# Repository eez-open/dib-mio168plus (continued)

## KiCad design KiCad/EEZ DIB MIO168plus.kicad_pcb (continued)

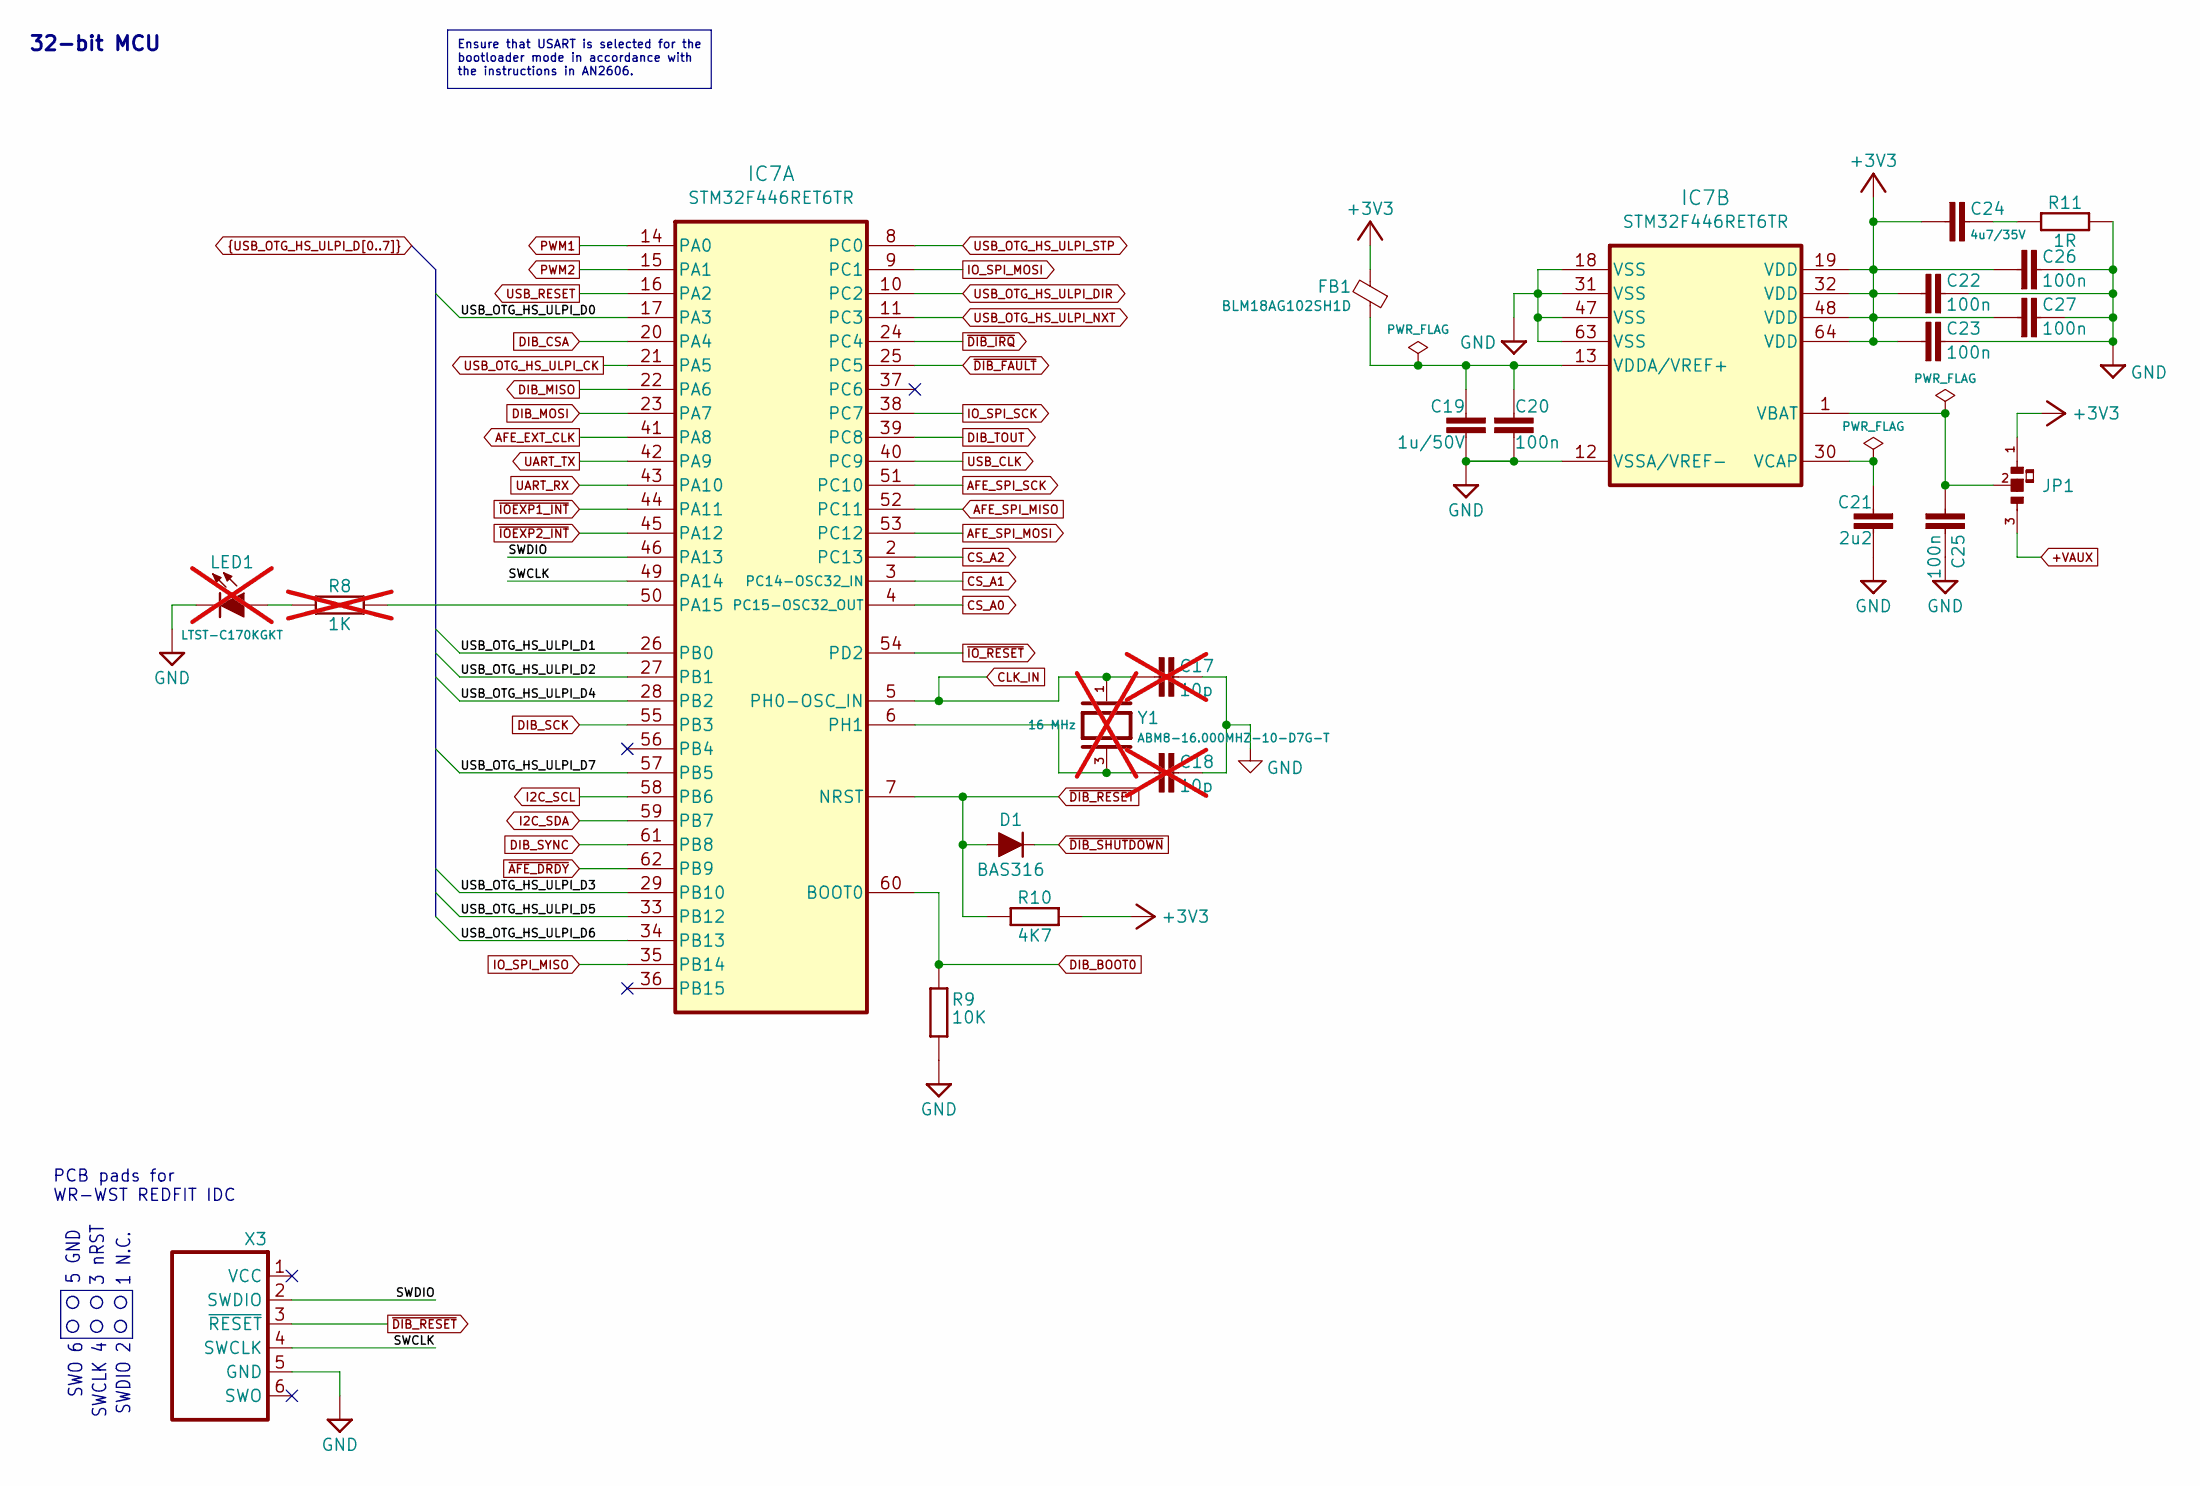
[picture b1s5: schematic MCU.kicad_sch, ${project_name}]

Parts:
C17, C18: 10p; C_0603_1608Metric; DigiKey 1276-1069-1-ND; not fitted
C19: 1u/50V; C_0603_1608Metric; DigiKey 1276-1860-1-ND
C20, C22, C23, C25, C26, C27: 100n; C_0603_1608Metric; DigiKey 490-4774-1-ND
C21: 2u2; C_0603_1608Metric; DigiKey 490-12738-1-ND
C24: 4u7/35V; C_0603_1608Metric; DigiKey 1276-6794-1-ND
D1: BAS316; SOD-323_1P8X1P35_ONS-M; DigiKey 1727-7370-1-ND
FB1: BLM18AG102SH1D; BEAD0603; DigiKey 490-7809-1-ND
IC7: STM32F446RET6TR; LQFP-64_10x10MM; DigiKey 497-STM32F446RET6TRCT-ND
JP1: JP3 shorted with 0R (0603)
LED1: LTST-C170KGKT; LED_LTST-C170KGKT_LTO-L; DigiKey 160-1414-2-ND; not fitted
R8: 1K; R_0603_1608Metric; DigiKey 13-RC0603FR-131KLCT-ND; not fitted
R9: 10K; R_0603_1608Metric; DigiKey 1712-CRGH0603F10KCT-ND
R10: 4K7; R_0603_1608Metric; DigiKey 13-RC0603FR-134K7LTR-ND
R11: 1R; R_0603_1608Metric; DigiKey 118-CHP0603QFW-1R00ELFCT-ND
X3: WR-WST_490107670612_DEBUG_pads
Y1: ABM8-16.000MHZ-10-D7G-T; XTAL_403C11A24M00000; DigiKey 535-14383-1-ND; not fitted

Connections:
+3V3: C22.1, C23.1, C24.1, C26.1, C27.1, FB1.2, IC7.19 (VDD), IC7.32 (VDD), IC7.48 (VDD), IC7.64 (VDD), JP1.1, R10.2; also elsewhere on the board
+VAUX: JP1.3; also elsewhere on the board
/MCU/SWCLK: IC7.49 (PA14), X3.4 (SWCLK)
/MCU/SWDIO: IC7.46 (PA13), X3.2 (SWDIO)
AFE_EXT_CLK: IC7.41 (PA8); also elsewhere on the board
AFE_SPI_MISO: IC7.52 (PC11); also elsewhere on the board
AFE_SPI_MOSI: IC7.53 (PC12); also elsewhere on the board
AFE_SPI_SCK: IC7.51 (PC10); also elsewhere on the board
CLK_IN: C17.2, IC7.5 (PH0-OSC_IN), Y1.1; also elsewhere on the board
CS_A0: IC7.4 (PC15-OSC32_OUT); also elsewhere on the board
CS_A1: IC7.3 (PC14-OSC32_IN); also elsewhere on the board
CS_A2: IC7.2 (PC13); also elsewhere on the board
DIB_BOOT0: IC7.60 (BOOT0), R9.2; also elsewhere on the board
DIB_CSA: IC7.20 (PA4); also elsewhere on the board
DIB_MISO: IC7.22 (PA6); also elsewhere on the board
DIB_MOSI: IC7.23 (PA7); also elsewhere on the board
DIB_SCK: IC7.55 (PB3); also elsewhere on the board
DIB_SYNC: IC7.61 (PB8); also elsewhere on the board
DIB_TOUT: IC7.39 (PC8); also elsewhere on the board
GND: C17.1, C18.1, C19.2, C20.2, C21.1, C22.2, C23.2, C25.1, C26.2, C27.2, IC7.12 (VSSA/VREF-), IC7.18 (VSS), IC7.31 (VSS), IC7.47 (VSS), IC7.63 (VSS), LED1.C, R9.1, R11.1, X3.5 (GND); also elsewhere on the board
I2C_SCL: IC7.58 (PB6); also elsewhere on the board
I2C_SDA: IC7.59 (PB7); also elsewhere on the board
IO_SPI_MISO: IC7.35 (PB14); also elsewhere on the board
IO_SPI_MOSI: IC7.9 (PC1); also elsewhere on the board
IO_SPI_SCK: IC7.38 (PC7); also elsewhere on the board
unnamed: C24.2, R11.2
unnamed: IC7.50 (PA15), R8.2
unnamed: C18.2, IC7.6 (PH1), Y1.3
unnamed: C25.2, IC7.1 (VBAT), JP1.2
unnamed: C21.2, IC7.30 (VCAP)
unnamed: C19.1, C20.1, FB1.1, IC7.13 (VDDA/VREF+)
unnamed: LED1.A, R8.1
PWM1: IC7.14 (PA0); also elsewhere on the board
PWM2: IC7.15 (PA1); also elsewhere on the board
UART_RX: IC7.43 (PA10); also elsewhere on the board
UART_TX: IC7.42 (PA9); also elsewhere on the board
USB_CLK: IC7.40 (PC9); also elsewhere on the board
USB_OTG_HS_ULPI_CK: IC7.21 (PA5); also elsewhere on the board
USB_OTG_HS_ULPI_D0: IC7.17 (PA3); also elsewhere on the board
USB_OTG_HS_ULPI_D1: IC7.26 (PB0); also elsewhere on the board
USB_OTG_HS_ULPI_D2: IC7.27 (PB1); also elsewhere on the board
USB_OTG_HS_ULPI_D3: IC7.29 (PB10); also elsewhere on the board
USB_OTG_HS_ULPI_D4: IC7.28 (PB2); also elsewhere on the board
USB_OTG_HS_ULPI_D5: IC7.33 (PB12); also elsewhere on the board
USB_OTG_HS_ULPI_D6: IC7.34 (PB13); also elsewhere on the board
USB_OTG_HS_ULPI_D7: IC7.57 (PB5); also elsewhere on the board
USB_OTG_HS_ULPI_DIR: IC7.10 (PC2); also elsewhere on the board
USB_OTG_HS_ULPI_NXT: IC7.11 (PC3); also elsewhere on the board
USB_OTG_HS_ULPI_STP: IC7.8 (PC0); also elsewhere on the board
USB_RESET: IC7.16 (PA2); also elsewhere on the board
~AFE_DRDY: IC7.62 (PB9); also elsewhere on the board
~DIB_FAULT: IC7.25 (PC5); also elsewhere on the board
~DIB_IRQ: IC7.24 (PC4); also elsewhere on the board
~DIB_RESET: D1.A, IC7.7 (NRST), R10.1, X3.3 (~RESET); also elsewhere on the board
~DIB_SHUTDOWN: D1.C; also elsewhere on the board
~IOEXP1_INT: IC7.44 (PA11); also elsewhere on the board
~IOEXP2_INT: IC7.45 (PA12); also elsewhere on the board
~IO_RESET: IC7.54 (PD2); also elsewhere on the board

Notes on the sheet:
3 nRST
SWO 6
32-bit MCU
SWCLK 4
SWDIO 2
1 N.C.
5 GND
PCB pads for WR-WST REDFIT IDC
Ensure that USART is selected for the bootloader mode in accordance with the instructions in AN2606.

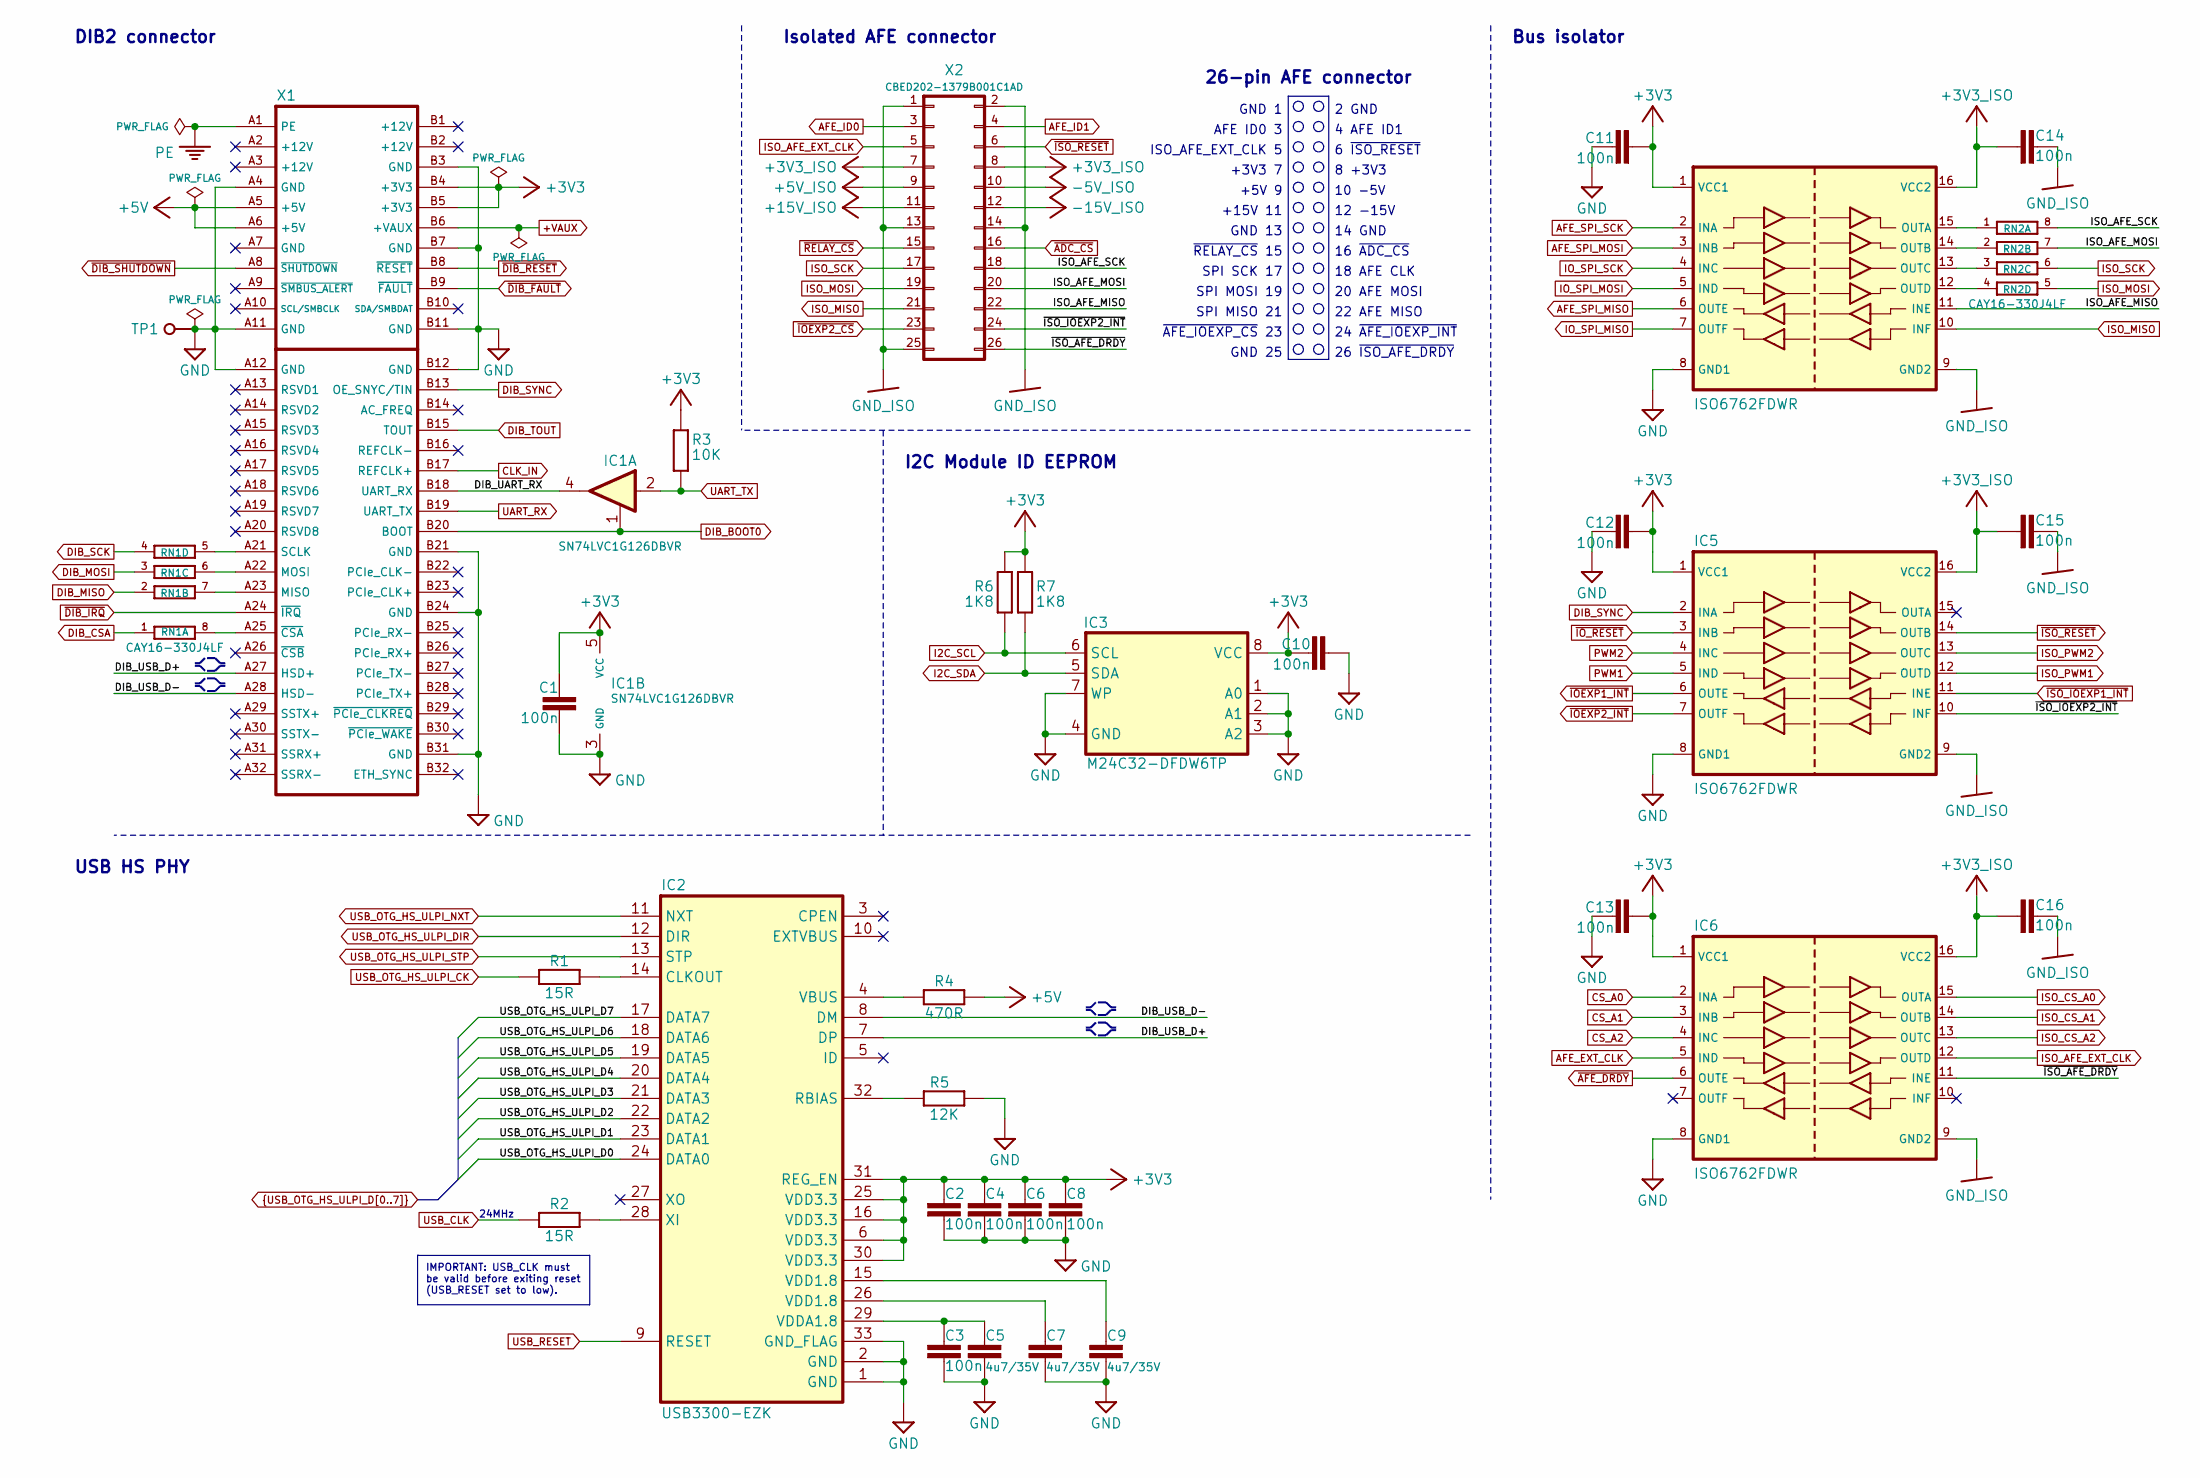
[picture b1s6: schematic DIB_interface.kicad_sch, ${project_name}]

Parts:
C1, C2, C3, C4, C6, C8, C10, C11, C12, C13, C14, C15, C16: 100n; C_0603_1608Metric; DigiKey 490-4774-1-ND
C5, C7, C9: 4u7/35V; C_0603_1608Metric; DigiKey 1276-6794-1-ND
IC1: SN74LVC1G126DBVR; DBV5; DigiKey 296-11605-1-ND
IC2: USB3300-EZK; QFN32_5X5MC_MCH-L; DigiKey 638-1034-ND
IC3: M24C32-DFDW6TP; TSSOP-8; DigiKey 497-16067-1-ND
IC4, IC5, IC6: ISO6762FDWR; DW16; DigiKey 296-ISO6762FDWRCT-ND
R1, R2: 15R; R_0603_1608Metric; DigiKey 13-AC0603FR-0715RLCT-ND
R3: 10K; R_0603_1608Metric; DigiKey 1712-CRGH0603F10KCT-ND
R4: 470R; R_0603_1608Metric; DigiKey 13-AC0603FR-7W470RLCT-ND
R5: 12K; R_0603_1608Metric; DigiKey 13-RC0603FR-1312KLCT-ND
R6, R7: 1K8; R_0603_1608Metric; DigiKey 13-RC0603FR-131K8LCT-ND
RN1, RN2: CAY16-330J4LF; CAY16; DigiKey CAY16-330J4LFCT-ND
TP1: Test; TEST-5
X1: DIB 2.0 edge card connector
X2: CBED202-1379B001C1AD; DigiKey 4217-CBED202-1379B001C1ADCT-ND

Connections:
+3V3: C1.1, C2.1, C4.1, C6.1, C8.1, C10.2, C11.1, C12.1, C13.1, IC1.5 (VCC), IC2.6 (VDD3.3), IC2.16 (VDD3.3), IC2.25 (VDD3.3), IC2.30 (VDD3.3), IC2.31 (REG_EN), IC3.8 (VCC), IC4.1 (VCC1), IC5.1 (VCC1), IC6.1 (VCC1), R3.2, R6.1, R7.1, X1.B4 (+3V3), X1.B5 (+3V3); also elsewhere on the board
+3V3_ISO: C14.2, C15.2, C16.2, IC4.16 (VCC2), IC5.16 (VCC2), IC6.16 (VCC2), X2.7, X2.8; also elsewhere on the board
+5V: R4.1, X1.A5 (+5V), X1.A6 (+5V); also elsewhere on the board
+5V_ISO: X2.9; also elsewhere on the board
+15V_ISO: X2.11; also elsewhere on the board
+VAUX: X1.B6 (+VAUX); also elsewhere on the board
-5V_ISO: X2.10; also elsewhere on the board
-15V_ISO: X2.12; also elsewhere on the board
/DIB2 interface, USB PHY/DIB_UART_RX: IC1.4 (Y), X1.B18 (UART_RX)
/DIB2 interface, USB PHY/DIB_USB_D+: IC2.7 (DP), X1.A27 (HSD+)
/DIB2 interface, USB PHY/DIB_USB_D-: IC2.8 (DM), X1.A28 (HSD-)
/DIB2 interface, USB PHY/ISO_AFE_MISO: IC4.11 (INE), X2.22
/DIB2 interface, USB PHY/ISO_AFE_MOSI: RN2.7 (2), X2.20
/DIB2 interface, USB PHY/ISO_AFE_SCK: RN2.8 (2), X2.18
/DIB2 interface, USB PHY/~ISO_AFE_DRDY: IC6.11 (INE), X2.26
/DIB2 interface, USB PHY/~ISO_IOEXP2_INT: IC5.10 (INF), X2.24
AFE_EXT_CLK: IC6.5 (IND); also elsewhere on the board
AFE_ID0: X2.3; also elsewhere on the board
AFE_ID1: X2.4; also elsewhere on the board
AFE_SPI_MISO: IC4.6 (OUTE); also elsewhere on the board
AFE_SPI_MOSI: IC4.3 (INB); also elsewhere on the board
AFE_SPI_SCK: IC4.2 (INA); also elsewhere on the board
CLK_IN: X1.B17 (REFCLK+); also elsewhere on the board
CS_A0: IC6.2 (INA); also elsewhere on the board
CS_A1: IC6.3 (INB); also elsewhere on the board
CS_A2: IC6.4 (INC); also elsewhere on the board
DIB_BOOT0: IC1.1 (OE), X1.B20 (BOOT); also elsewhere on the board
DIB_CSA: RN1.1; also elsewhere on the board
DIB_MISO: RN1.2 (1); also elsewhere on the board
DIB_MOSI: RN1.3 (1); also elsewhere on the board
DIB_SCK: RN1.4 (1); also elsewhere on the board
DIB_SYNC: IC5.2 (INA), X1.B13 (OE_SNYC/TIN); also elsewhere on the board
DIB_TOUT: X1.B15 (TOUT); also elsewhere on the board
GND: C1.2, C2.2, C3.2, C4.2, C5.2, C6.2, C7.2, C8.2, C9.2, C10.1, C11.2, C12.2, C13.2, IC1.3 (GND), IC2.1 (GND), IC2.2 (GND), IC2.33 (GND_FLAG), IC3.1 (A0), IC3.2 (A1), IC3.3 (A2), IC3.4 (GND), IC3.7 (WP), IC4.8 (GND1), IC5.8 (GND1), IC6.8 (GND1), R5.1, TP1.1 (P$1_1), X1.A4 (GND), X1.A11 (GND), X1.A12 (GND), X1.B3 (GND), X1.B7 (GND), X1.B11 (GND), X1.B12 (GND), X1.B21 (GND), X1.B24 (GND), X1.B31 (GND); also elsewhere on the board
GND_ISO: C14.1, C15.1, C16.1, IC4.9 (GND2), IC5.9 (GND2), IC6.9 (GND2), X2.1, X2.2, X2.13, X2.14, X2.25; also elsewhere on the board
I2C_SCL: IC3.6 (SCL), R6.2; also elsewhere on the board
I2C_SDA: IC3.5 (SDA), R7.2; also elsewhere on the board
IO_SPI_MISO: IC4.7 (OUTF); also elsewhere on the board
IO_SPI_MOSI: IC4.5 (IND); also elsewhere on the board
IO_SPI_SCK: IC4.4 (INC); also elsewhere on the board
ISO_AFE_EXT_CLK: IC6.12 (OUTD), X2.5
ISO_CS_A0: IC6.15 (OUTA); also elsewhere on the board
ISO_CS_A1: IC6.14 (OUTB); also elsewhere on the board
ISO_CS_A2: IC6.13 (OUTC); also elsewhere on the board
ISO_MISO: IC4.10 (INF), X2.21; also elsewhere on the board
ISO_MOSI: RN2.5 (2), X2.19; also elsewhere on the board
ISO_PWM1: IC5.12 (OUTD); also elsewhere on the board
ISO_PWM2: IC5.13 (OUTC); also elsewhere on the board
ISO_SCK: RN2.6 (2), X2.17; also elsewhere on the board
unnamed: C7.1, IC2.26 (VDD1.8)
unnamed: C9.1, IC2.15 (VDD1.8)
unnamed: IC2.14 (CLKOUT), R1.1
unnamed: IC2.32 (RBIAS), R5.2
unnamed: IC2.4 (VBUS), R4.2
unnamed: C3.1, C5.1, IC2.29 (VDDA1.8)
unnamed: IC2.28 (XI), R2.1
unnamed: IC4.15 (OUTA), RN2.1
unnamed: IC4.14 (OUTB), RN2.2 (1)
unnamed: IC4.13 (OUTC), RN2.3 (1)
unnamed: IC4.12 (OUTD), RN2.4 (1)
unnamed: RN1.8 (2), X1.A25 (~CSA)
unnamed: RN1.7 (2), X1.A23 (MISO)
unnamed: RN1.6 (2), X1.A22 (MOSI)
unnamed: RN1.5 (2), X1.A21 (SCLK)
PE: X1.A1 (PE); also elsewhere on the board
PWM1: IC5.5 (IND); also elsewhere on the board
PWM2: IC5.4 (INC); also elsewhere on the board
UART_RX: X1.B19 (UART_TX); also elsewhere on the board
UART_TX: IC1.2 (A), R3.1; also elsewhere on the board
USB_CLK: R2.2; also elsewhere on the board
USB_OTG_HS_ULPI_CK: R1.2; also elsewhere on the board
USB_OTG_HS_ULPI_D0: IC2.24 (DATA0); also elsewhere on the board
USB_OTG_HS_ULPI_D1: IC2.23 (DATA1); also elsewhere on the board
USB_OTG_HS_ULPI_D2: IC2.22 (DATA2); also elsewhere on the board
USB_OTG_HS_ULPI_D3: IC2.21 (DATA3); also elsewhere on the board
USB_OTG_HS_ULPI_D4: IC2.20 (DATA4); also elsewhere on the board
USB_OTG_HS_ULPI_D5: IC2.19 (DATA5); also elsewhere on the board
USB_OTG_HS_ULPI_D6: IC2.18 (DATA6); also elsewhere on the board
USB_OTG_HS_ULPI_D7: IC2.17 (DATA7); also elsewhere on the board
USB_OTG_HS_ULPI_DIR: IC2.12 (DIR); also elsewhere on the board
USB_OTG_HS_ULPI_NXT: IC2.11 (NXT); also elsewhere on the board
USB_OTG_HS_ULPI_STP: IC2.13 (STP); also elsewhere on the board
USB_RESET: IC2.9 (RESET); also elsewhere on the board
~ADC_CS: X2.16; also elsewhere on the board
~AFE_DRDY: IC6.6 (OUTE); also elsewhere on the board
~DIB_FAULT: X1.B9 (~FAULT); also elsewhere on the board
~DIB_IRQ: X1.A24 (~IRQ); also elsewhere on the board
~DIB_RESET: X1.B8 (~RESET); also elsewhere on the board
~DIB_SHUTDOWN: X1.A8 (~SHUTDOWN); also elsewhere on the board
~IOEXP1_INT: IC5.6 (OUTE); also elsewhere on the board
~IOEXP2_CS: X2.23; also elsewhere on the board
~IOEXP2_INT: IC5.7 (OUTF); also elsewhere on the board
~IO_RESET: IC5.3 (INB); also elsewhere on the board
~ISO_IOEXP1_INT: IC5.11 (INE); also elsewhere on the board
~ISO_RESET: IC5.14 (OUTB), X2.6; also elsewhere on the board
~RELAY_CS: X2.15; also elsewhere on the board

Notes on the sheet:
~{RELAY_CS} 15
6 ~{ISO_RESET}
2 GND
SPI SCK 17
18 AFE CLK
22 AFE MISO
4 AFE ID1
SPI MOSI 19
+15V 11
10 -5V
20 AFE MOSI
24 ~{AFE_IOEXP_INT}
GND 25
USB HS PHY
GND 1
AFE ID0 3
26-pin AFE connector
Isolated AFE connector
~{AFE_IOEXP_CS} 23
+5V 9
DIB2 connector
24MHz
ISO_AFE_EXT_CLK 5
12 -15V
I2C Module ID EEPROM
GND 13
+3V3 7
SPI MISO 21
14 GND
8 +3V3
26 ~{ISO_AFE_DRDY}
16 ~{ADC_CS}
Bus isolator
IMPORTANT: USB_CLK must be valid before exiting reset (USB_RESET set to low).

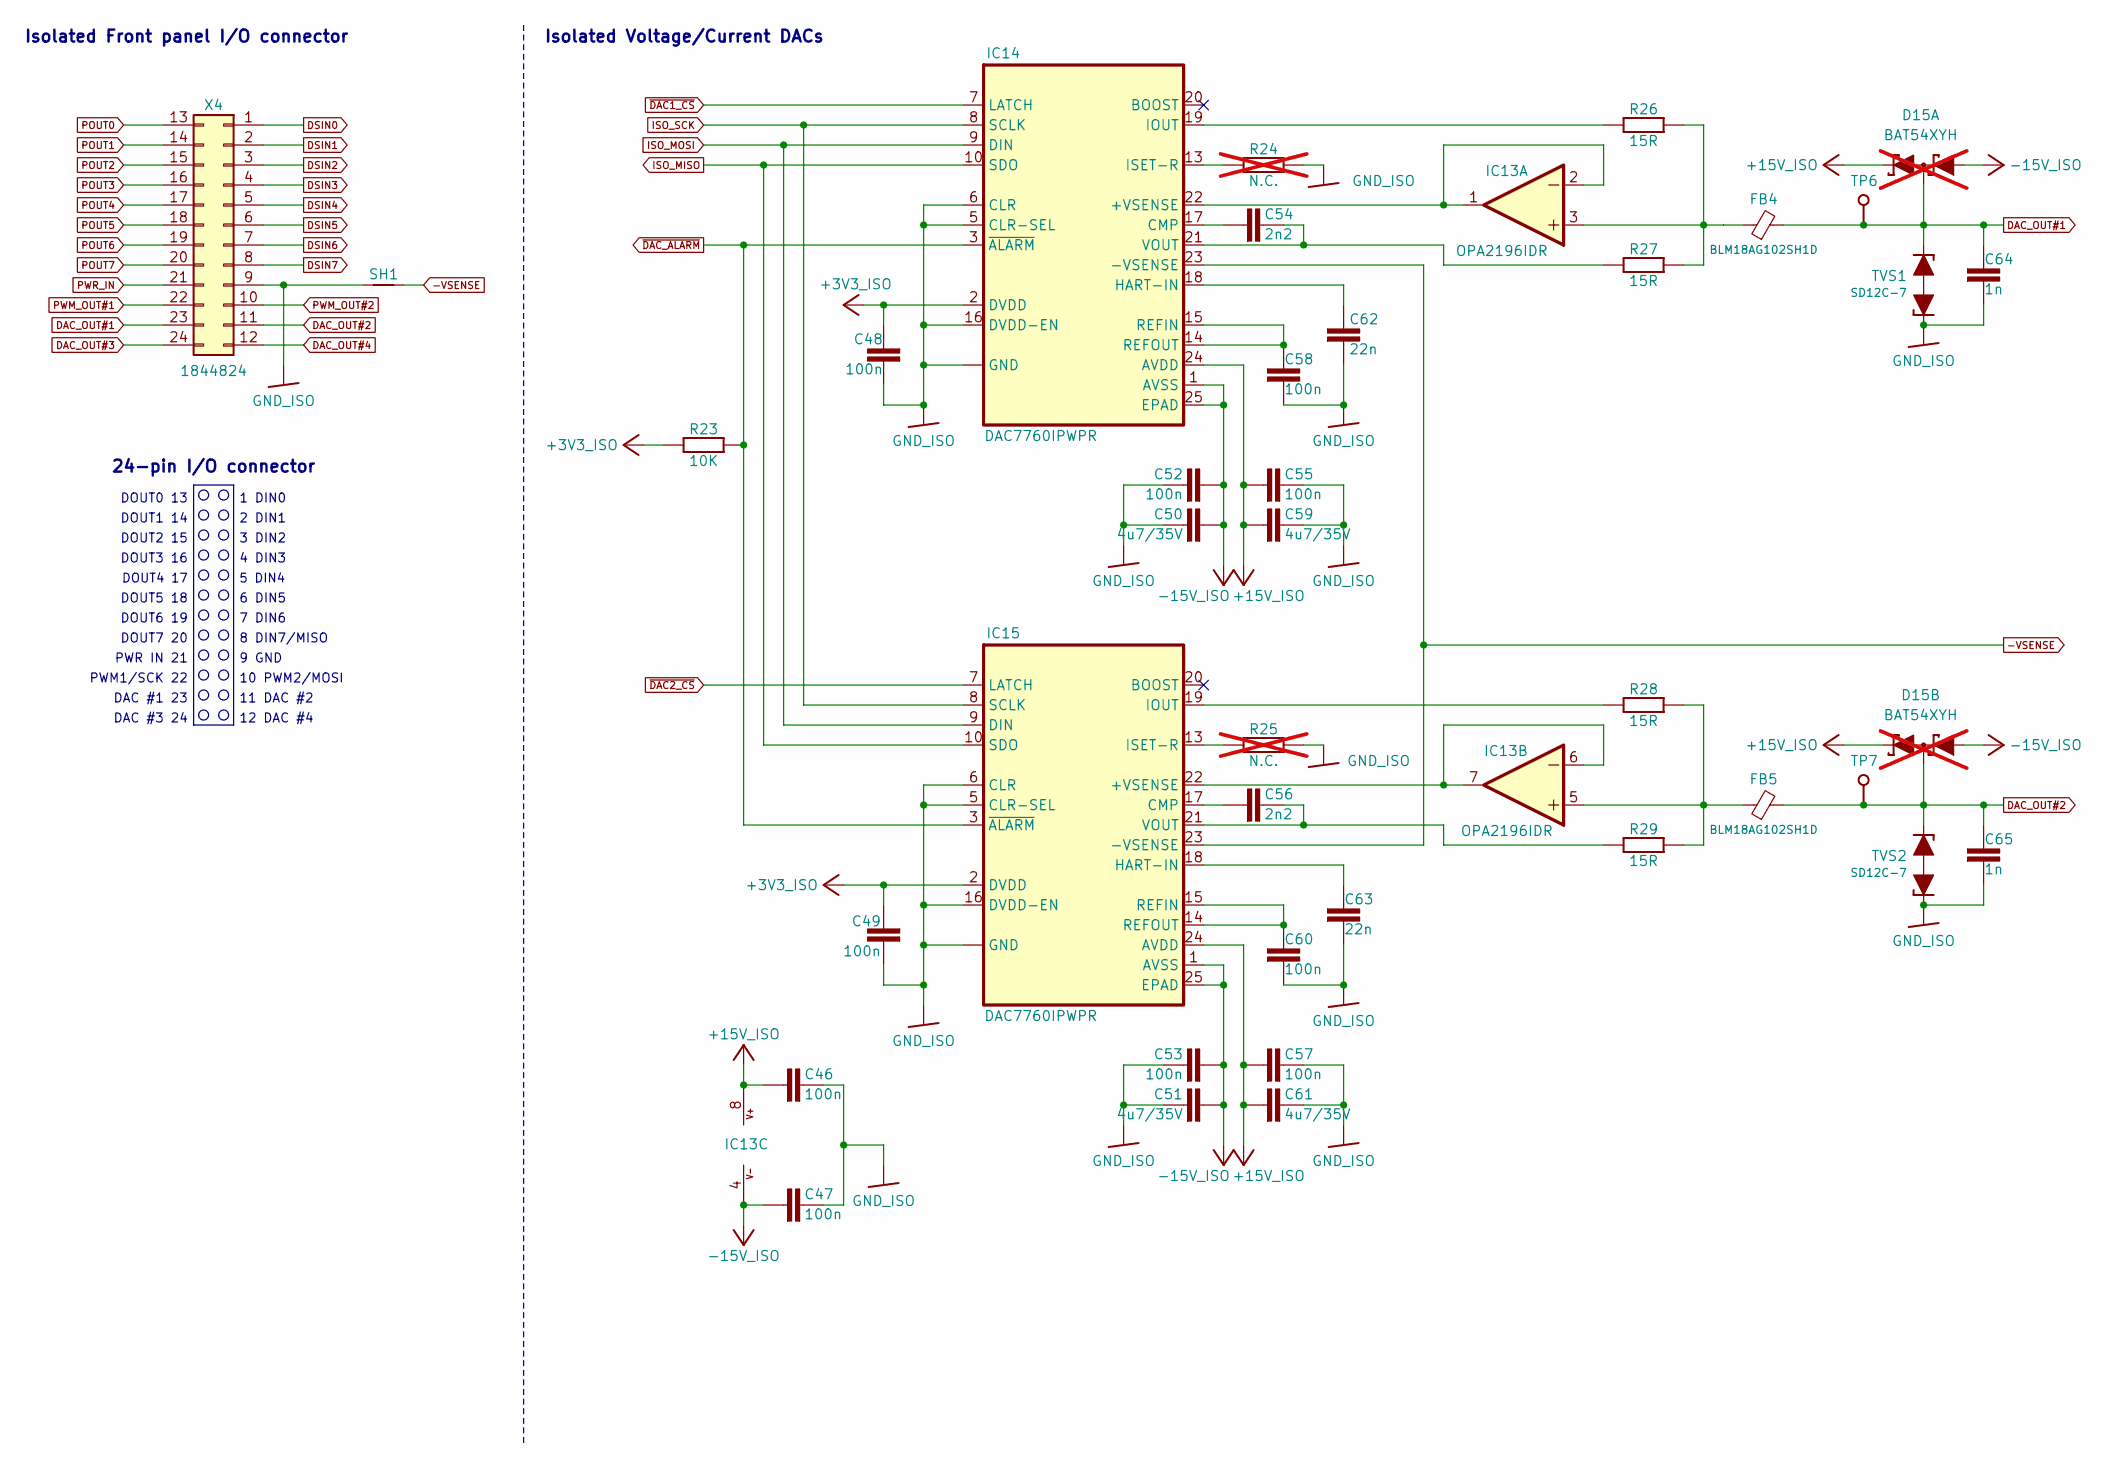
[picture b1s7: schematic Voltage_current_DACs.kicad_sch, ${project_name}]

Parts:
C46, C47, C48, C49, C52, C53, C55, C57, C58, C60: 100n; C_0603_1608Metric; DigiKey 490-4774-1-ND
C50, C51, C59, C61: 4u7/35V; C_0603_1608Metric; DigiKey 1276-6794-1-ND
C54, C56: 2n2; C_0603_1608Metric; DigiKey 490-4931-1-ND
C62, C63: 22n; C_0603_1608Metric; DigiKey 490-4933-1-ND
C64, C65: 1n; C_0603_1608Metric; DigiKey 1276-1018-2-ND
D15: BAT54XYH; SOP65P210X110-6N; DigiKey 1727-2723-1-ND; not fitted
FB4, FB5: BLM18AG102SH1D; BEAD0603; DigiKey 490-7809-1-ND
IC13: OPA2196IDR; SOIC127P600X173-8N; DigiKey 296-48159-1-ND
IC14, IC15: DAC7760IPWPR; PWP24; DigiKey 296-37188-1-ND
R23: 10K; R_0603_1608Metric; DigiKey 1712-CRGH0603F10KCT-ND
R24, R25: N.C.; R_0603_1608Metric; not fitted
R26, R27, R28, R29: 15R; R_0603_1608Metric; DigiKey 13-AC0603FR-0715RLCT-ND
SH1: SHORTNOHOLE; NetTie-2_SMD_Pad0.5mm
TP6, TP7: Test; Testhole 24_50mils
TVS1, TVS2: SD12C-7; SOD-323_PESD; DigiKey 31-SD12C-7CT-ND
X4: 1844824; DigiKey 1844824-ND

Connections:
+3V3_ISO: C48.1, C49.1, IC14.2 (DVDD), IC15.2 (DVDD), R23.1; also elsewhere on the board
+15V_ISO: C46.1, C55.1, C57.1, C59.2, C61.2, D15.2 (K2), D15.5 (K3), IC13.8 (V+), IC14.24 (AVDD), IC15.24 (AVDD); also elsewhere on the board
-15V_ISO: C47.1, C50.2, C51.2, C52.1, C53.1, D15.1 (A1), D15.4 (A4), IC13.4 (V-), IC14.1 (AVSS), IC14.25 (EPAD), IC15.1 (AVSS), IC15.25 (EPAD); also elsewhere on the board
-VSENSE: IC14.23 (-VSENSE), IC15.23 (-VSENSE), SH1.2
DAC_OUT#1: C64.1, D15.6 (K1A2), FB4.2, TP6.1 (P$1_1), TVS1.C2 (2), X4.23
DAC_OUT#2: C65.1, D15.3 (A3K4), FB5.2, TP7.1 (P$1_1), TVS2.C2 (2), X4.11
DAC_OUT#3: X4.24; also elsewhere on the board
DAC_OUT#4: X4.12; also elsewhere on the board
DSIN0: X4.1; also elsewhere on the board
DSIN1: X4.2; also elsewhere on the board
DSIN2: X4.3; also elsewhere on the board
DSIN3: X4.4; also elsewhere on the board
DSIN4: X4.5; also elsewhere on the board
DSIN5: X4.6; also elsewhere on the board
DSIN6: X4.7; also elsewhere on the board
DSIN7: X4.8; also elsewhere on the board
GND_ISO: C46.2, C47.2, C48.2, C49.2, C50.1, C51.1, C52.2, C53.2, C55.2, C57.2, C58.2, C59.1, C60.2, C61.1, C62.1, C63.1, C64.2, C65.2, IC14.4 (GND), IC14.5 (CLR-SEL), IC14.6 (CLR), IC14.11 (GND), IC14.12 (GND), IC14.16 (DVDD-EN), IC15.4 (GND), IC15.5 (CLR-SEL), IC15.6 (CLR), IC15.11 (GND), IC15.12 (GND), IC15.16 (DVDD-EN), R24.1, R25.2, SH1.1, TVS1.C1 (1), TVS2.C1 (1), X4.9; also elsewhere on the board
ISO_MISO: IC14.10 (SDO), IC15.10 (SDO); also elsewhere on the board
ISO_MOSI: IC14.9 (DIN), IC15.9 (DIN); also elsewhere on the board
ISO_SCK: IC14.8 (SCLK), IC15.8 (SCLK); also elsewhere on the board
unnamed: FB4.1, IC13.3 (+IN), R26.1, R27.1
unnamed: IC13.1 (OUT), IC13.2 (-IN), IC14.22 (+VSENSE)
unnamed: FB5.1, IC13.5 (+IN), R28.1, R29.1
unnamed: IC13.6 (-IN), IC13.7 (OUT), IC15.22 (+VSENSE)
unnamed: C54.2, IC14.17 (CMP)
unnamed: C62.2, IC14.18 (HART-IN)
unnamed: IC14.19 (IOUT), R26.2
unnamed: IC14.13 (ISET-R), R24.2
unnamed: C58.1, IC14.14 (REFOUT), IC14.15 (REFIN)
unnamed: C54.1, IC14.21 (VOUT), R27.2
unnamed: C56.2, IC15.17 (CMP)
unnamed: C63.2, IC15.18 (HART-IN)
unnamed: IC15.19 (IOUT), R28.2
unnamed: IC15.13 (ISET-R), R25.1
unnamed: C60.1, IC15.14 (REFOUT), IC15.15 (REFIN)
unnamed: C56.1, IC15.21 (VOUT), R29.2
POUT0: X4.13; also elsewhere on the board
POUT1: X4.14; also elsewhere on the board
POUT2: X4.15; also elsewhere on the board
POUT3: X4.16; also elsewhere on the board
POUT4: X4.17; also elsewhere on the board
POUT5: X4.18; also elsewhere on the board
POUT6: X4.19; also elsewhere on the board
POUT7: X4.20; also elsewhere on the board
PWM_OUT#1: X4.22; also elsewhere on the board
PWM_OUT#2: X4.10; also elsewhere on the board
PWR_IN: X4.21; also elsewhere on the board
~DAC1_CS: IC14.7 (LATCH); also elsewhere on the board
~DAC2_CS: IC15.7 (LATCH); also elsewhere on the board
~DAC_ALARM: IC14.3 (~ALARM), IC15.3 (~ALARM), R23.2; also elsewhere on the board

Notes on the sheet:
Isolated Voltage/Current DACs
1 DIN0
9 GND
DAC #1 23
DAC #3 24
DOUT2 15
6 DIN5
24-pin I/O connector
PWR IN 21
12 DAC #4
DOUT3 16
DOUT7 20
3 DIN2
4 DIN3
8 DIN7/MISO
DOUT5 18
11 DAC #2
2 DIN1
DOUT1 14
5 DIN4
Isolated Front panel I/O connector
7 DIN6
PWM1/SCK 22
DOUT6 19
DOUT4 17
DOUT0 13
10 PWM2/MOSI

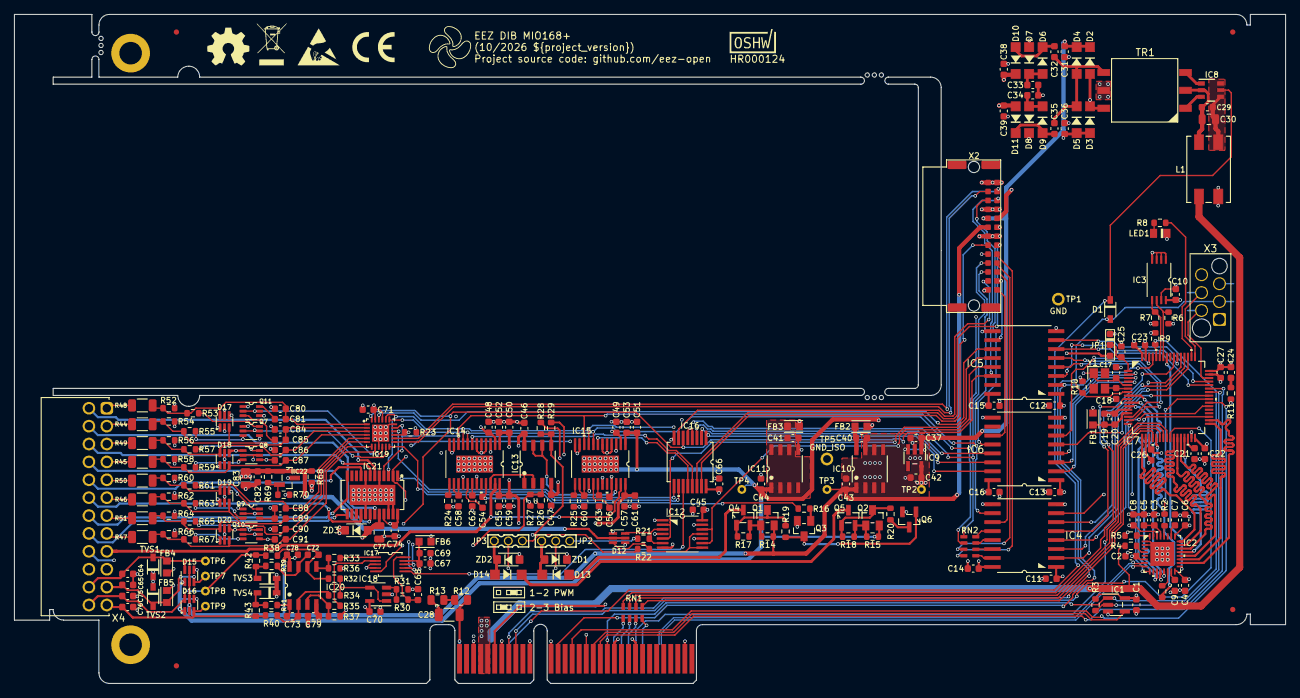
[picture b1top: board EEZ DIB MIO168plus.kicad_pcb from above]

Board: 4 copper layers, 180.5 x 95.0 mm, 262 parts (0 on the bottom side), 218 nets.

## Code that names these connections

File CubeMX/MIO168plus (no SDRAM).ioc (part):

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Mcu.Name=STM32F446R(C-E)Tx
Mcu.Package=LQFP64
Mcu.UserName=STM32F446RETx
PA0-WKUP.GPIOParameters=GPIO_Label
PA0-WKUP.GPIO_Label=PWM1
PA0-WKUP.Signal=S_TIM2_CH1_ETR
PA1.GPIOParameters=GPIO_Label
PA1.GPIO_Label=PWM2
PA1.Signal=S_TIM2_CH2
PA10.Mode=Asynchronous
PA10.Signal=USART1_RX
PA11.GPIOParameters=GPIO_Label
PA11.GPIO_Label=IOEXP1_INT
PA11.Signal=GPXTI11
PA12.GPIOParameters=GPIO_Label
PA12.GPIO_Label=IOEXP2_INT
PA12.Signal=GPXTI12
PA13.Mode=Serial_Wire
PA13.Signal=SYS_JTMS-SWDIO
PA14.Mode=Serial_Wire
PA14.Signal=SYS_JTCK-SWCLK
PA15.GPIOParameters=GPIO_Label
PA15.GPIO_Label=TEST_OUT
PA15.Signal=GPIO_Output
PA2.GPIOParameters=GPIO_Label
PA2.GPIO_Label=USB_RESET
PA2.Signal=GPIO_Output
PA3.Mode=Device_HS
PA3.Signal=USB_OTG_HS_ULPI_D0
PA4.GPIOParameters=GPIO_Label
PA4.GPIO_Label=DIB_CSA
PA4.Mode=NSS_Signal_Hard_Input
PA4.Signal=SPI1_NSS
PA5.Mode=Device_HS
PA5.Signal=USB_OTG_HS_ULPI_CK
PA6.GPIOParameters=GPIO_Label
PA6.GPIO_Label=DIB_MISO
PA6.Mode=Full_Duplex_Slave
PA6.Signal=SPI1_MISO
PA7.GPIOParameters=GPIO_Label
PA7.GPIO_Label=DIB_MOSI
PA7.Mode=Full_Duplex_Slave
PA7.Signal=SPI1_MOSI
PA8.GPIOParameters=GPIO_Label
PA8.GPIO_Label=AFE_EXT_CLK
PA8.Mode=Clock-out-1
PA8.Signal=RCC_MCO_1
PA9.Mode=Asynchronous
PA9.Signal=USART1_TX
PB0.Mode=Device_HS
PB0.Signal=USB_OTG_HS_ULPI_D1
PB1.Mode=Device_HS
PB1.Signal=USB_OTG_HS_ULPI_D2
PB10.Mode=Device_HS
PB10.Signal=USB_OTG_HS_ULPI_D3
PB12.Mode=Device_HS
PB12.Signal=USB_OTG_HS_ULPI_D5
PB13.Mode=Device_HS
PB13.Signal=USB_OTG_HS_ULPI_D6
PB14.GPIOParameters=GPIO_Label
PB14.GPIO_Label=IO_SPI_MISO
PB14.Mode=Full_Duplex_Master
PB14.Signal=SPI2_MISO
PB2.Mode=Device_HS
PB2.Signal=USB_OTG_HS_ULPI_D4
PB3.GPIOParameters=GPIO_Label
PB3.GPIO_Label=DIB_SCK
PB3.Mode=Full_Duplex_Slave
PB3.Signal=SPI1_SCK
PB5.Mode=Device_HS
PB5.Signal=USB_OTG_HS_ULPI_D7
PB6.Mode=I2C
PB6.Signal=I2C1_SCL
PB7.Mode=I2C
PB7.Signal=I2C1_SDA
PB8.GPIOParameters=GPIO_Label
PB8.GPIO_Label=DIB_OE_SYNC
PB8.Signal=GPXTI8
PB9.GPIOParameters=GPIO_Label
PB9.GPIO_Label=AFE_DRDY
PB9.Signal=GPXTI9
PC0.Mode=Device_HS
PC0.Signal=USB_OTG_HS_ULPI_STP
PC1.GPIOParameters=GPIO_Label
PC1.GPIO_Label=IO_SPI_MOSI
PC1.Mode=Full_Duplex_Master
PC1.Signal=SPI2_MOSI
PC10.GPIOParameters=GPIO_Label
PC10.GPIO_Label=AFE_SPI_SCK
PC10.Mode=Full_Duplex_Master
PC10.Signal=SPI3_SCK
PC11.GPIOParameters=GPIO_Label
PC11.GPIO_Label=AFE_SPI_MISO
PC11.Mode=Full_Duplex_Master
PC11.Signal=SPI3_MISO
PC12.GPIOParameters=GPIO_Label
PC12.GPIO_Label=AFE_SPI_MOSI
PC12.Mode=Full_Duplex_Master
PC12.Signal=SPI3_MOSI
PC13.GPIOParameters=GPIO_Label
PC13.GPIO_Label=CS_A2
PC13.Signal=GPIO_Output
PC14-OSC32_IN.GPIOParameters=GPIO_Label
PC14-OSC32_IN.GPIO_Label=CS_A1
PC14-OSC32_IN.Signal=GPIO_Output
PC15-OSC32_OUT.GPIOParameters=GPIO_Label
PC15-OSC32_OUT.GPIO_Label=CS_A0
PC15-OSC32_OUT.Signal=GPIO_Output
PC2.Mode=Device_HS
PC2.Signal=USB_OTG_HS_ULPI_DIR
PC3.Mode=Device_HS
PC3.Signal=USB_OTG_HS_ULPI_NXT
PC4.GPIOParameters=GPIO_Label
PC4.GPIO_Label=DIB_IRQ
PC4.Signal=GPXTI4
PC5.GPIOParameters=GPIO_Label
PC5.GPIO_Label=DIB_FAULT
PC5.Signal=GPIO_Output
PC7.GPIOParameters=GPIO_Label
PC7.GPIO_Label=IO_SPI_SCK
PC7.Mode=Full_Duplex_Master
PC7.Signal=SPI2_SCK
PC8.GPIOParameters=GPIO_Label
PC8.GPIO_Label=DIB_TOUT
PC8.Signal=GPIO_Output
PC9.GPIOParameters=GPIO_Label
PC9.GPIO_Label=USB_CLK
PC9.Mode=Clock-out-2
PC9.Signal=RCC_MCO_2
PD2.GPIOParameters=GPIO_Label
PD2.GPIO_Label=IO_RESET
PD2.Signal=GPIO_Output
PH0-OSC_IN.Mode=HSE-External-Clock-Source
PH0-OSC_IN.Signal=RCC_OSC_IN
PH1-OSC_OUT.Mode=HSE-External-Clock-Source
PH1-OSC_OUT.Signal=RCC_OSC_OUT
RCC.HSE_VALUE=10000000
RCC.SYSCLKFreq_VALUE=180000000
RCC.SYSCLKSource=RCC_SYSCLKSOURCE_PLLRCLK
board=custom

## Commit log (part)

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2026-05-16 README.md added
